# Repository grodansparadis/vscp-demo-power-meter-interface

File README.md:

# VSCP power system demo

*This is work in progress.*

This is demo code for a power monitoring system for a house incuding an office. It uses the 

  * [Accra counter module](https://www.grodansparadis.com/accra/accra.html) 
  * [Vilnius A/D module](http://www.grodansparadis.com/vilnius/vilnius.html) 
  * [Kelvin NTC10K](http://www.grodansparadis.com/kelvinntc10k/kelvin_ntc10ka.html)
  
from [Grodans Paradis AB](https://www.grodansparadis.com). 

This code is part of the [VSCP project](https://www.vscp.org).

License is [MIT](https://www.google.com/url?sa=t&rct=j&q=&esrc=s&source=web&cd=4&cad=rja&uact=8&ved=2ahUKEwiO2Mv4y_7cAhUFM5oKHSkxA90QFjADegQIBhAB&url=https%3A%2F%2Fopensource.org%2Flicenses%2FMIT&usg=AOvVaw1MsEPekvPKCIceu2jiRDy4)

Copyright 2018 [Ake Hedman, Grodans Paradis AB](akhe@grodansparadis.com)

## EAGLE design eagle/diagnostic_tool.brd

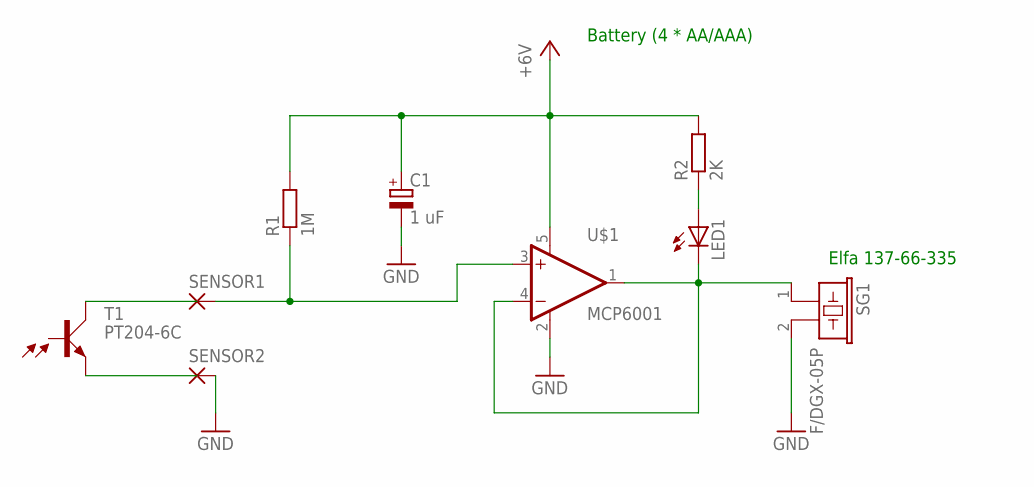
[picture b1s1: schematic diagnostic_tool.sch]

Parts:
C1: 1 uF; E2,5-5
LED1: LED; SMARTLED-TTW
R1: 1M; 0207/10
R2: 2K; 0207/10
SENSOR1, SENSOR2: WIREPAD1,6/0,8; 1,6/0,8
SG1: F/DGX-05P; B/C11L
T1: PT204-6C; BP103
U$1: MCP6001; SOT23-5L

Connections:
+5V: C1.+, R1.2, R2.2, U$1.5 (V+)
GND: C1.-, SENSOR2.1, SG1.2, U$1.2 (V-)
unnamed: LED1.A@1 (A), R2.1
unnamed: LED1.C@1 (C), SG1.1, U$1.1 (OUT), U$1.4 (-IN)
unnamed: R1.1, SENSOR1.1, U$1.3 (+IN)

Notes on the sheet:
Battery (4 * AA/AAA)
Elfa 137-66-335

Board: 2 copper layers, 9 parts (0 on the bottom side), 5 nets, no tracks yet.

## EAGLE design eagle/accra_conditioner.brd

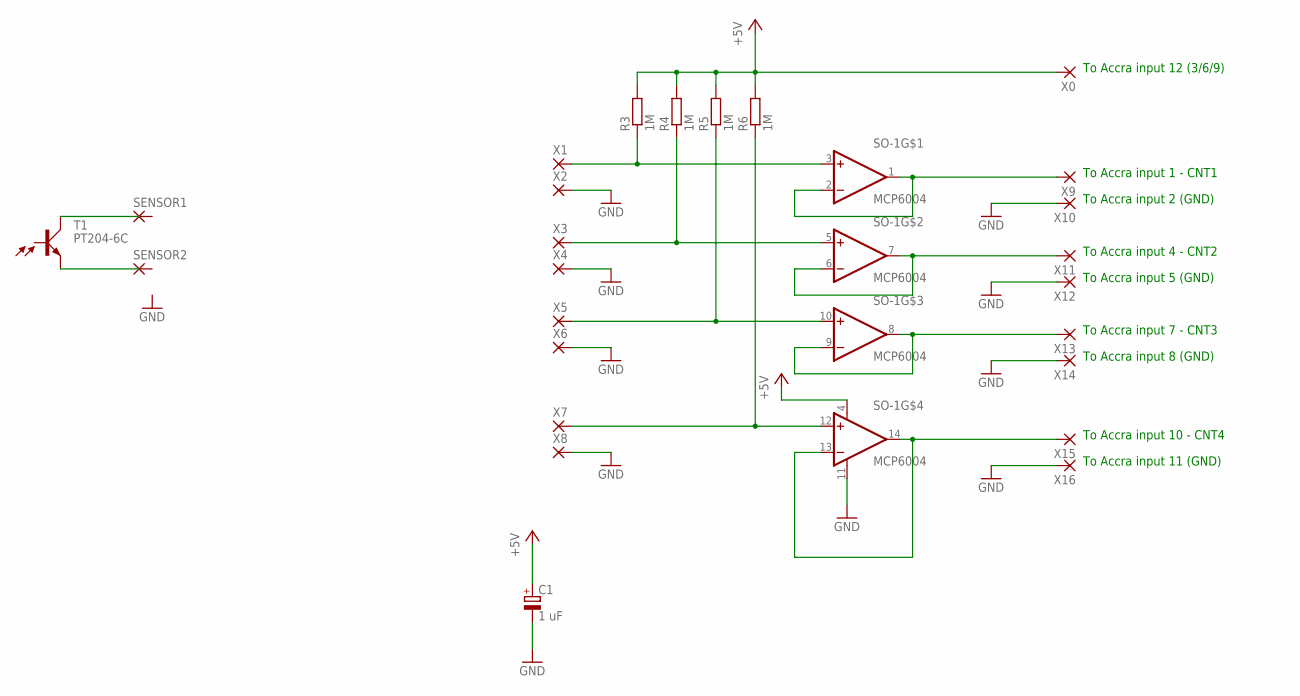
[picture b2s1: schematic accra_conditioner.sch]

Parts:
C1: 1 uF; E2,5-5
R3, R4, R5, R6: 1M; 0207/10
SENSOR1, SENSOR2: WIREPAD1,6/0,8; 1,6/0,8
SO-1: MCP6004; SO-14
T1: PT204-6C; BP103
X0, X1, X2, X3, X4, X5, X6, X7, X8, X9, X10, X11, X12, X13, X14, X15, X16: WIREPAD1,6/0,8; 1,6/0,8

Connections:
+5V: C1.+, R3.2, R4.2, R5.2, R6.2, SO-1.4 (V+), X0.1
GND: C1.-, SO-1.11 (V-), X2.1, X4.1, X6.1, X8.1, X10.1, X12.1, X14.1, X16.1
unnamed: R3.1, SO-1.3 (+IN), X1.1
unnamed: R4.1, SO-1.5 (+IN), X3.1
unnamed: SO-1.1 (OUT), SO-1.2 (-IN), X9.1
unnamed: SO-1.6 (-IN), SO-1.7 (OUT), X11.1
unnamed: R5.1, SO-1.10 (+IN), X5.1
unnamed: R6.1, SO-1.12 (+IN), X7.1
unnamed: SO-1.8 (OUT), SO-1.9 (-IN), X13.1
unnamed: SO-1.13 (-IN), SO-1.14 (OUT), X15.1

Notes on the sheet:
To Accra input 1 - CNT1
To Accra input 2 (GND)
To Accra input 4 - CNT2
To Accra input 5 (GND)
To Accra input 7 - CNT3
To Accra input 8 (GND)
To Accra input 10 - CNT4
To Accra input 11 (GND)
To Accra input 12 (3/6/9)

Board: 2 copper layers, 26 parts (0 on the bottom side), 10 nets, no tracks yet.

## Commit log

2020-10-08 Initial checkin
2020-10-08 Merged with old project (vscp-demo-power)
2020-10-12 Fixed buffer amp.
